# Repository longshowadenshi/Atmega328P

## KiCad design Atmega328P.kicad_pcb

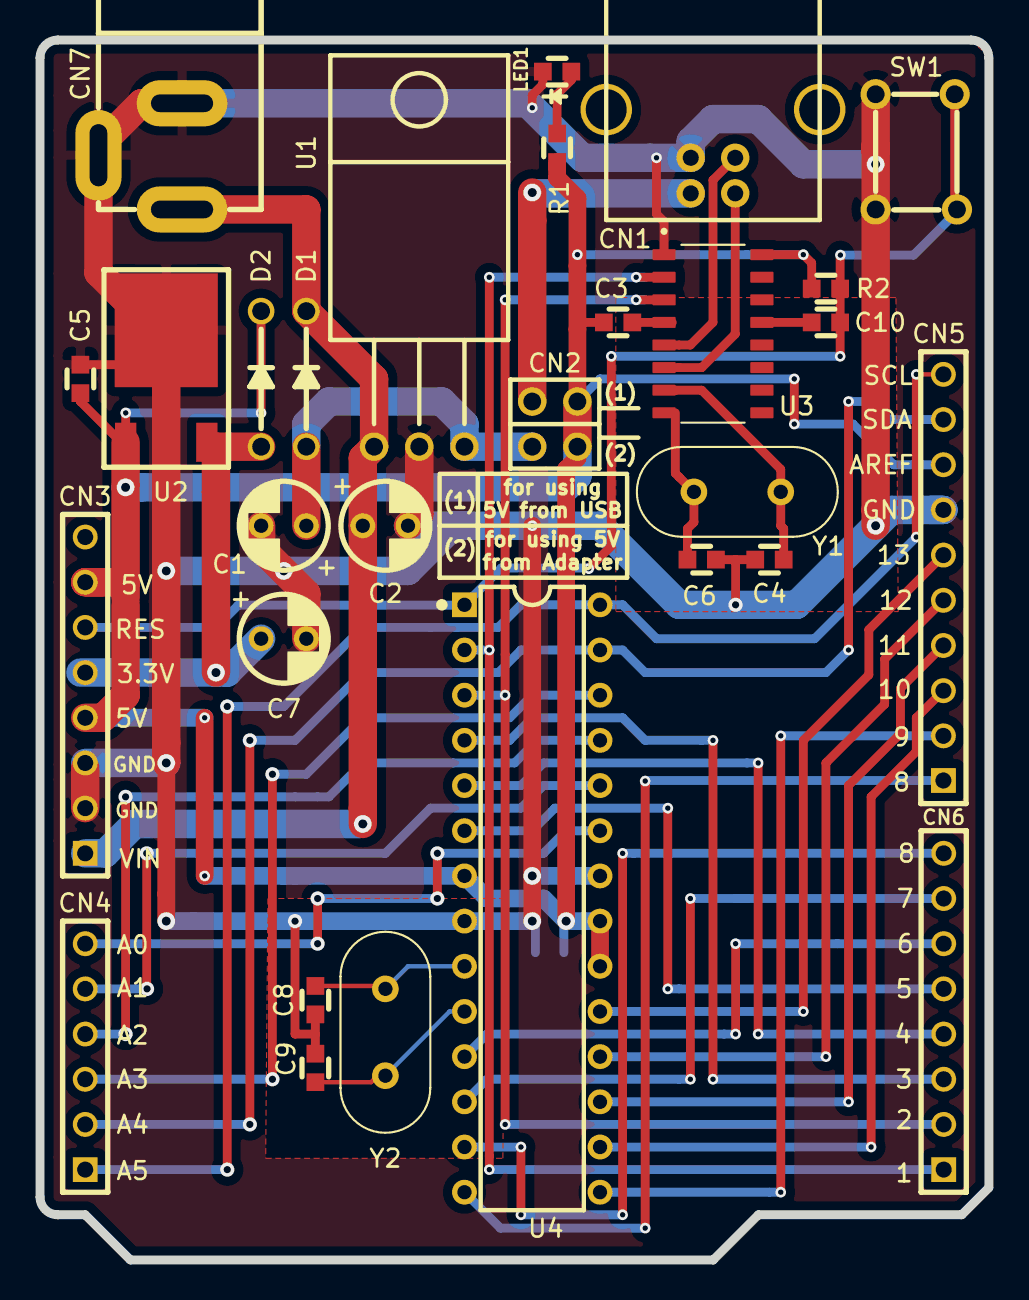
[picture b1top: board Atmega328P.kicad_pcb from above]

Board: 2 copper layers, 53.3 x 68.6 mm, 30 parts (1 on the bottom side), 36 nets.

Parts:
C1, C2, C7: 10uf; 10uF-16v
C3, C5, C10: 1uf; C0603C104Z3VACTU
C4, C6, C8, C9: 22pF; C0603C104Z3VACTU
C11: 0.1uf; C0603C104Z3VACTU
CN1: USB-B
CN2: jumper
CN3: CN_8pins_pwr; cn_8pins_L
CN4: CN_6pins; cn_6pins
CN5: CN_10pins; cn
CN6: CN_8pins; cn_8pins
CN7: MJ-179P; MJ179P
D1, D2: 1S4; 1DS4
LED1: LED; C0603C104Z3VACTU
R1: 330; C0603C104Z3VACTU
R2: 10k; C0603C104Z3VACTU
SW1: SKHHBY
U1: NJM78M05FA
U2: NJM2391DL1-33; njm2391dl1-33
U3: CH340G; SOIC127P600X180-16N
U4: Atmega328P; Atmega328p
Y1: 12MHz; Crystal_HC49-U_Vertical
Y2: 16MHz; Crystal_HC49-U_Vertical

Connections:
+3V3: C7.1, CN3.5, D2.1, U2.3
+5V: C3.1, C5.1, C11.1, CN2.2, CN2.4, CN3.4, CN3.7, CN5.8, D2.2, R1.1, R2.1, U2.1, U3.16, U4.7, U4.20, U4.21
/5v_USB: CN1.1, CN2.1
/A0: CN4.6, U4.23
/A1: CN4.5, U4.24
/A2: CN4.4, U4.25
/A3: CN4.3, U4.26
/A4: CN4.2, CN5.9, U4.27
/A5: CN4.1, CN5.10, U4.28
/D2: CN6.3, U4.4
/D3: CN6.4, U4.5
/D4: CN6.5, U4.6
/D5: CN6.6, U4.11
/D6: CN6.7, U4.12
/D7: CN6.8, U4.13
/D8: CN5.1, U4.14
/D9: CN5.2, U4.15
/D10: CN5.3, U4.16
/D11: CN5.4, U4.17
/D12: CN5.5, U4.18
/D13: CN5.6, U4.19
/RESET: C10.1, CN3.6, R2.2, SW1.3, SW1.4, U4.1
/RX: CN6.1, U3.2, U4.2
/TX: CN6.2, U3.3, U4.3
/Vin: C1.1, CN3.1, CN7.1, D1.2, U1.1
GND: C1.2, C2.2, C4.2, C5.2, C6.2, C7.2, C8.2, C9.2, C11.2, CN1.4, CN3.2, CN3.3, CN5.7, CN7.2, CN7.3, LED1.2, SW1.1, SW1.2, U1.2, U2.2, U3.1, U4.8, U4.22
unnamed: C2.1, CN2.3, D1.1, U1.3
unnamed: C3.2, U3.4
unnamed: C4.1, U3.7, Y1.1
unnamed: C6.1, U3.8, Y1.2
unnamed: C8.1, U4.9, Y2.1
unnamed: C9.1, U4.10, Y2.2
unnamed: C10.2, U3.13
unnamed: CN1.2, U3.6
unnamed: CN1.3, U3.5
unnamed: LED1.1, R1.2
